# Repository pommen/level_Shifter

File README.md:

# level_Shifter
5->24->5 volt level shifter using jellybean components.

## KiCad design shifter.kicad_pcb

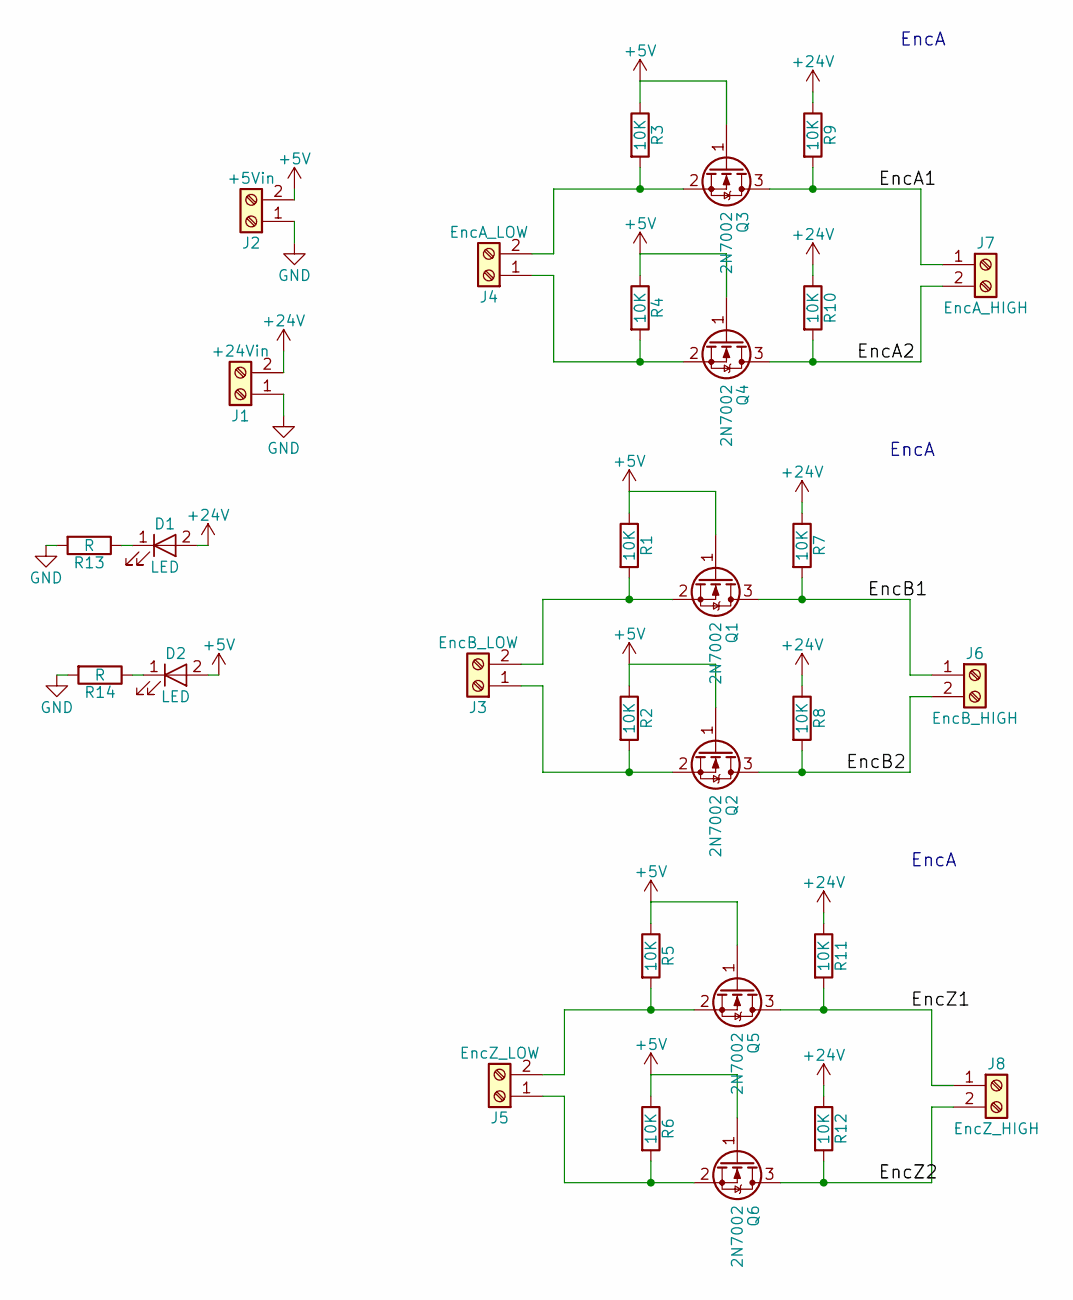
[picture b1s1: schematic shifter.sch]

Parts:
D1, D2: LED; LED_0805_HandSoldering
J1: +24Vin; TerminalBlock_bornier-2_P5.08mm
J2: +5Vin; TerminalBlock_bornier-2_P5.08mm
J3: EncB_LOW; TerminalBlock_bornier-2_P5.08mm
J4: EncA_LOW; TerminalBlock_bornier-2_P5.08mm
J5: EncZ_LOW; TerminalBlock_bornier-2_P5.08mm
J6: EncB_HIGH; TerminalBlock_bornier-2_P5.08mm
J7: EncA_HIGH; TerminalBlock_bornier-2_P5.08mm
J8: EncZ_HIGH; TerminalBlock_bornier-2_P5.08mm
Q1, Q2, Q3, Q4, Q5, Q6: 2N7002; SOT-23
R1, R2, R3, R4, R5, R6, R7, R8, R9, R10, R11, R12: 10K; R_0805_HandSoldering
R13, R14: R; R_0805_HandSoldering

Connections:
+5V: D2.2 (A), J2.2, Q1.1 (G), Q2.1 (G), Q3.1 (G), Q4.1 (G), Q5.1 (G), Q6.1 (G), R1.1, R2.1, R3.1, R4.1, R5.1, R6.1
+24V: D1.2 (A), J1.2, R7.1, R8.1, R9.1, R10.1, R11.1, R12.1
/EncA1: J7.1, Q3.3 (D), R9.2
/EncA2: J7.2, Q4.3 (D), R10.2
/EncB1: J6.1, Q1.3 (D), R7.2
/EncB2: J6.2, Q2.3 (D), R8.2
/EncZ1: J8.1, Q5.3 (D), R11.2
/EncZ2: J8.2, Q6.3 (D), R12.2
GND: J1.1, J2.1, R13.2, R14.2
unnamed: D1.1 (K), R13.1
unnamed: D2.1 (K), R14.1
unnamed: J3.1, Q2.2 (S), R2.2
unnamed: J3.2, Q1.2 (S), R1.2
unnamed: J4.1, Q4.2 (S), R4.2
unnamed: J4.2, Q3.2 (S), R3.2
unnamed: J5.1, Q6.2 (S), R6.2
unnamed: J5.2, Q5.2 (S), R5.2

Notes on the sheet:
EncA

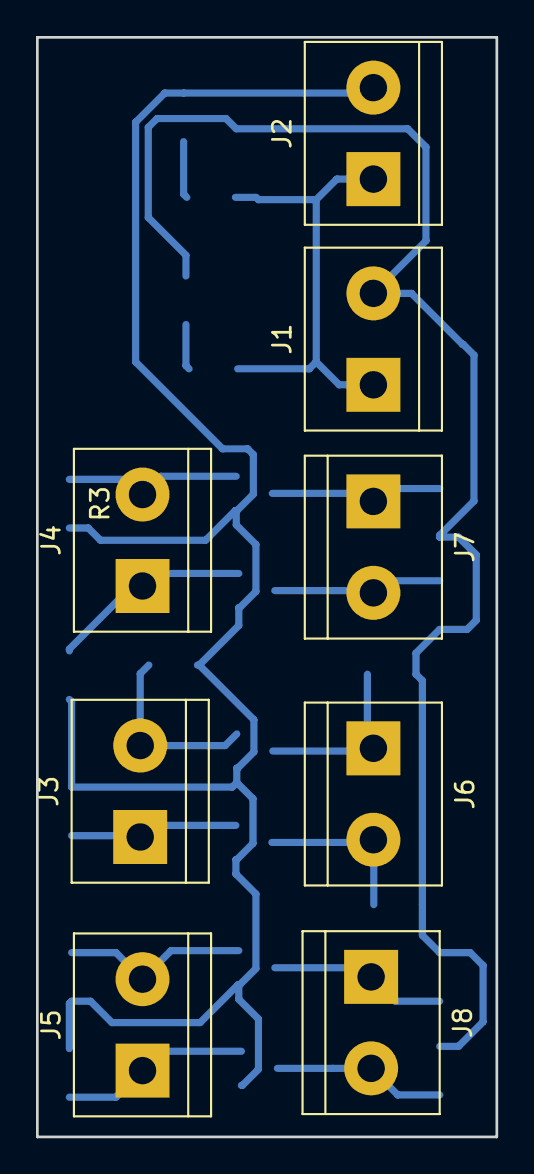
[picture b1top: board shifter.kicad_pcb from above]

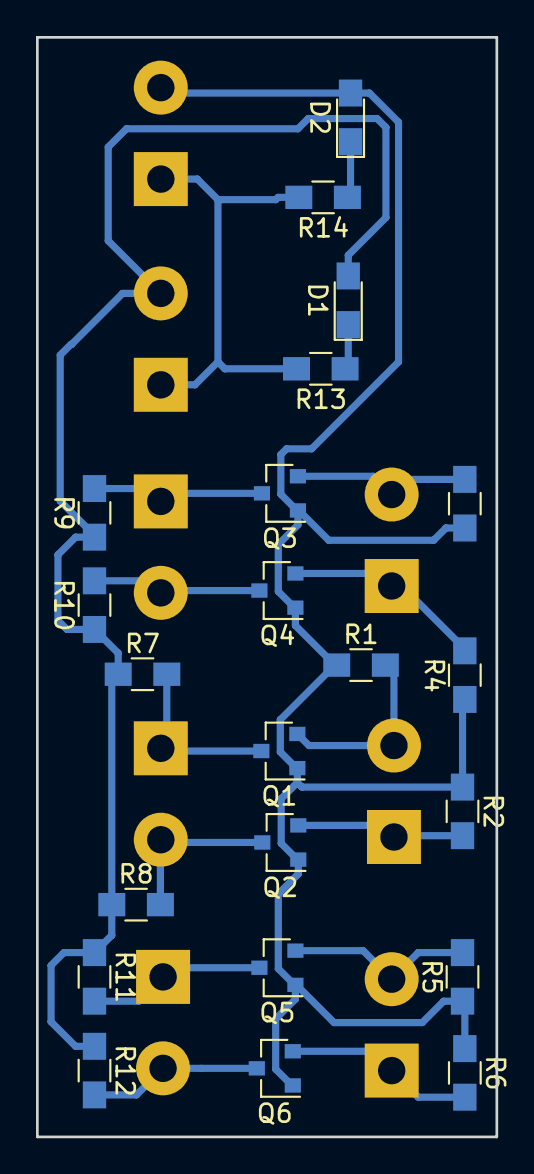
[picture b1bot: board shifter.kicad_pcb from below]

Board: 2 copper layers, 25.5 x 61.1 mm, 30 parts (22 on the bottom side), 17 nets.

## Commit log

2018-02-27 kicad schmatic and layout
